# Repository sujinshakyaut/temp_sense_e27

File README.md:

# Thermal Monitoring Module (E27)

A compact multi-channel temperature sensing PCB built around the TI MSPM0C1104 microcontroller with CAN FD communication. Designed to be later integrated on a voltage tap board that mounts directly onto the Orion BMS module, providing up to 24 analog temperature inputs per tapboard or breakout board multiplexed through a 3 ADC channel with robust power protection for automotive and industrial environments.

## Table of Contents

- [Background](#background)
- [NTC Thermistors & Steinhart-Hart](#ntc-thermistors--steinhart-hart)
- [Validation & Troubleshooting](#validation--troubleshooting)
- [Features](#features)
- [Contributing](#contributing)
- [License](#license)

## Background

This is a redesigned temperature sensing board intended to be integrated with a voltage tap board on the Orion BMS module, providing cell temperature monitoring across the battery pack. 

The main Orion BMS is limited to 8 internal thermistor inputs, which is insufficient for large-scale battery packs. To achieve full coverage, we integrated the Orion Thermistor Expansion Module, scaling our monitoring capacity to 60+ individual cells. This expansion node digitizes localized analog temperatures and broadcasts them via CANbus to the main unit. This architecture not only meets the capacity requirements of the accumulator but also ensures clean data transmission and minimizes wiring complexity within the high-voltage enclosure.

The board consolidates power regulation, input protection, analog multiplexing, and CAN FD communication onto a single compact PCB. A three-stage power supply has been implemented due to potential 60V voltage spikes from the battery module. Power input is protected by an LM74500 ideal diode controller and an SMF24CA TVS diode, with the AP63205 buck converter stepping down to 5 V and a TPS7A03 LDO providing a clean 3.3 V rail. A fuse is included for extra protection.

The CLV4051A 8:1 analog multiplexer allows a single ADC input on the MSPM0C to scan up to 8 temperature sensor channels sequentially, reducing pin count. The MCP2517FD provides CAN FD connectivity over SPI.

## NTC Thermistors & Steinhart-Hart

This board interfaces with Negative Temperature Coefficient (NTC) thermistors (typically 10 kΩ at 25°C). The thermistors are placed in a voltage divider circuit with a known 10 kΩ bias resistor. Because the resistance curve of an NTC is highly non-linear, the firmware utilizes the Steinhart-Hart equation for accurate conversion from resistance to temperature across the accumulator's operating range:

$$\frac{1}{T} = A + B \ln(R) + C (\ln(R))^3$$

Where:
* T = Temperature in Kelvin
* R = Measured resistance of the thermistor in Ohms
* A, B, C = Steinhart-Hart coefficients provided by the thermistor manufacturer

The MCU reads the 12-bit ADC value, calculates the resistance R via the voltage divider equation, applies the Steinhart-Hart conversion to find Kelvin, and then broadcasts the Celsius equivalent over CAN FD.

## Features

- 24-channel analog temperature input via CLV4051A multiplexers
- CAN FD communication (MCP2517FD over SPI) to Orion BMS
- Wide input voltage range with reverse polarity and TVS protection
- On-board buck + LDO three-stage power supply with 24V voltage regulation
- High-accuracy NTC thermistor reading using Steinhart-Hart conversion
- Screw terminal connectors
- M3 mounting holes for panel or DIN mount

## Contributing

Open an issue or pull request on [GitHub](https://github.com/sujinshakyaut/temp_sense_e27).

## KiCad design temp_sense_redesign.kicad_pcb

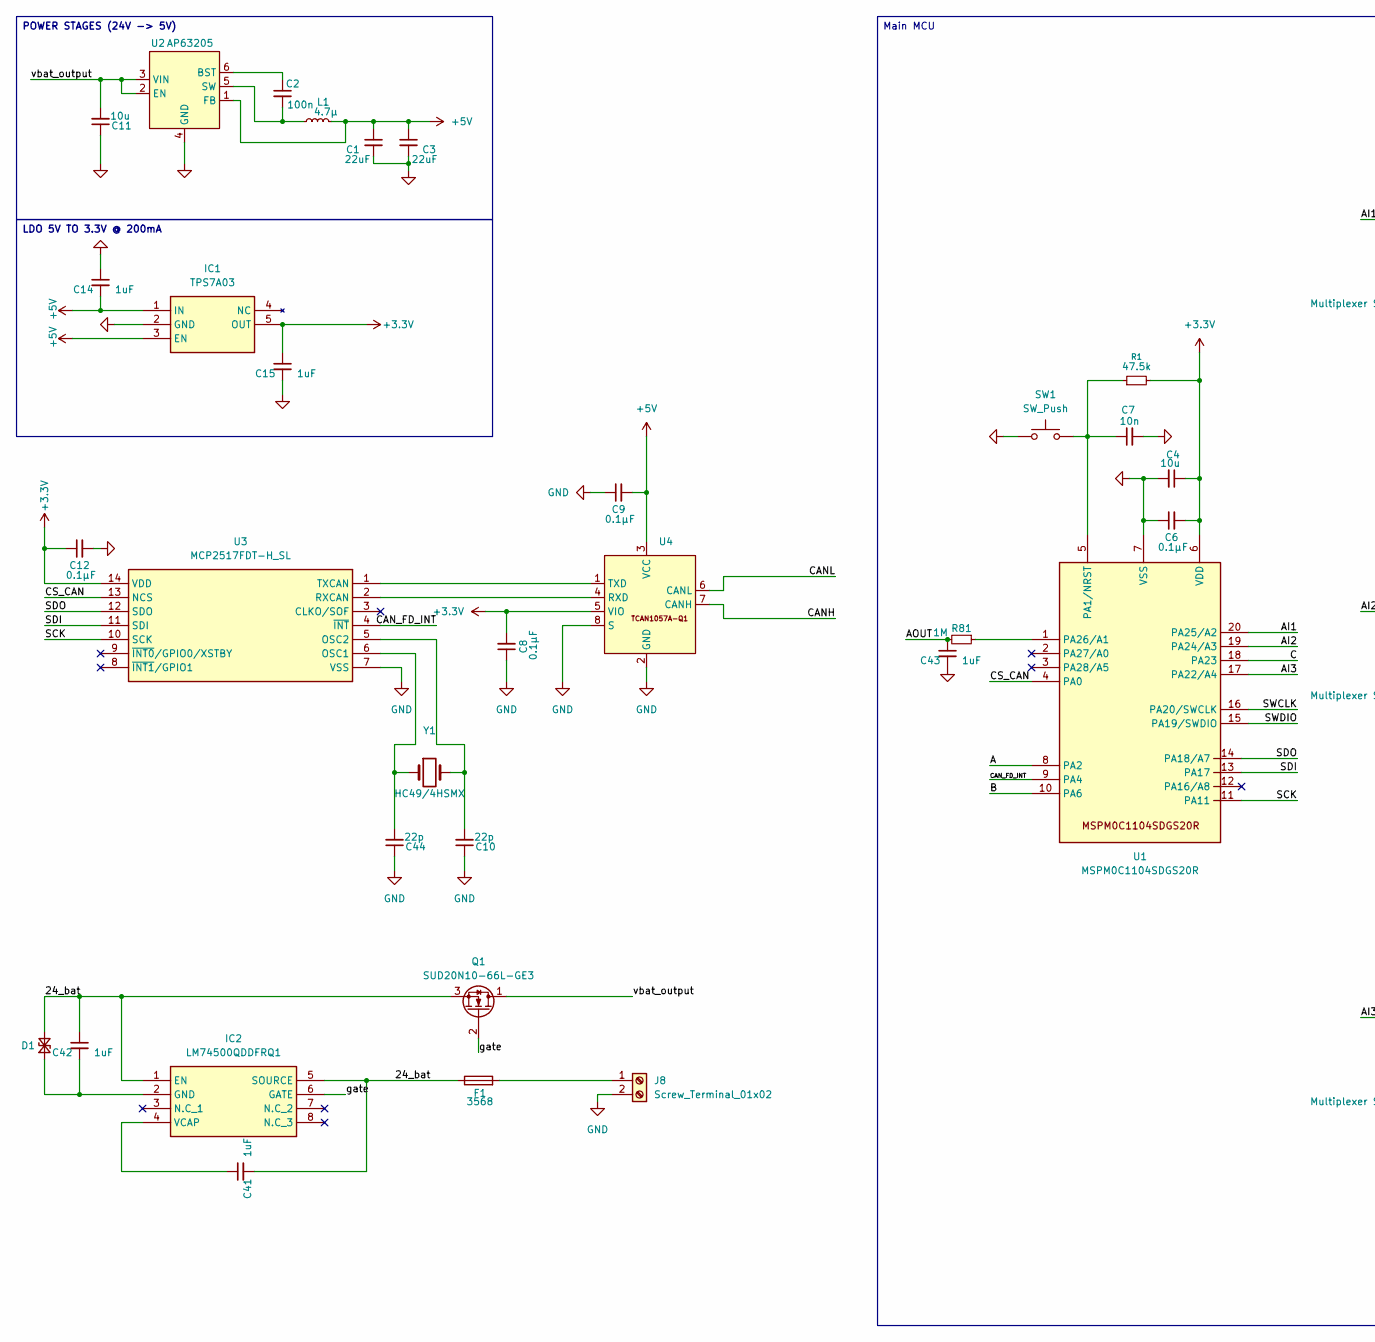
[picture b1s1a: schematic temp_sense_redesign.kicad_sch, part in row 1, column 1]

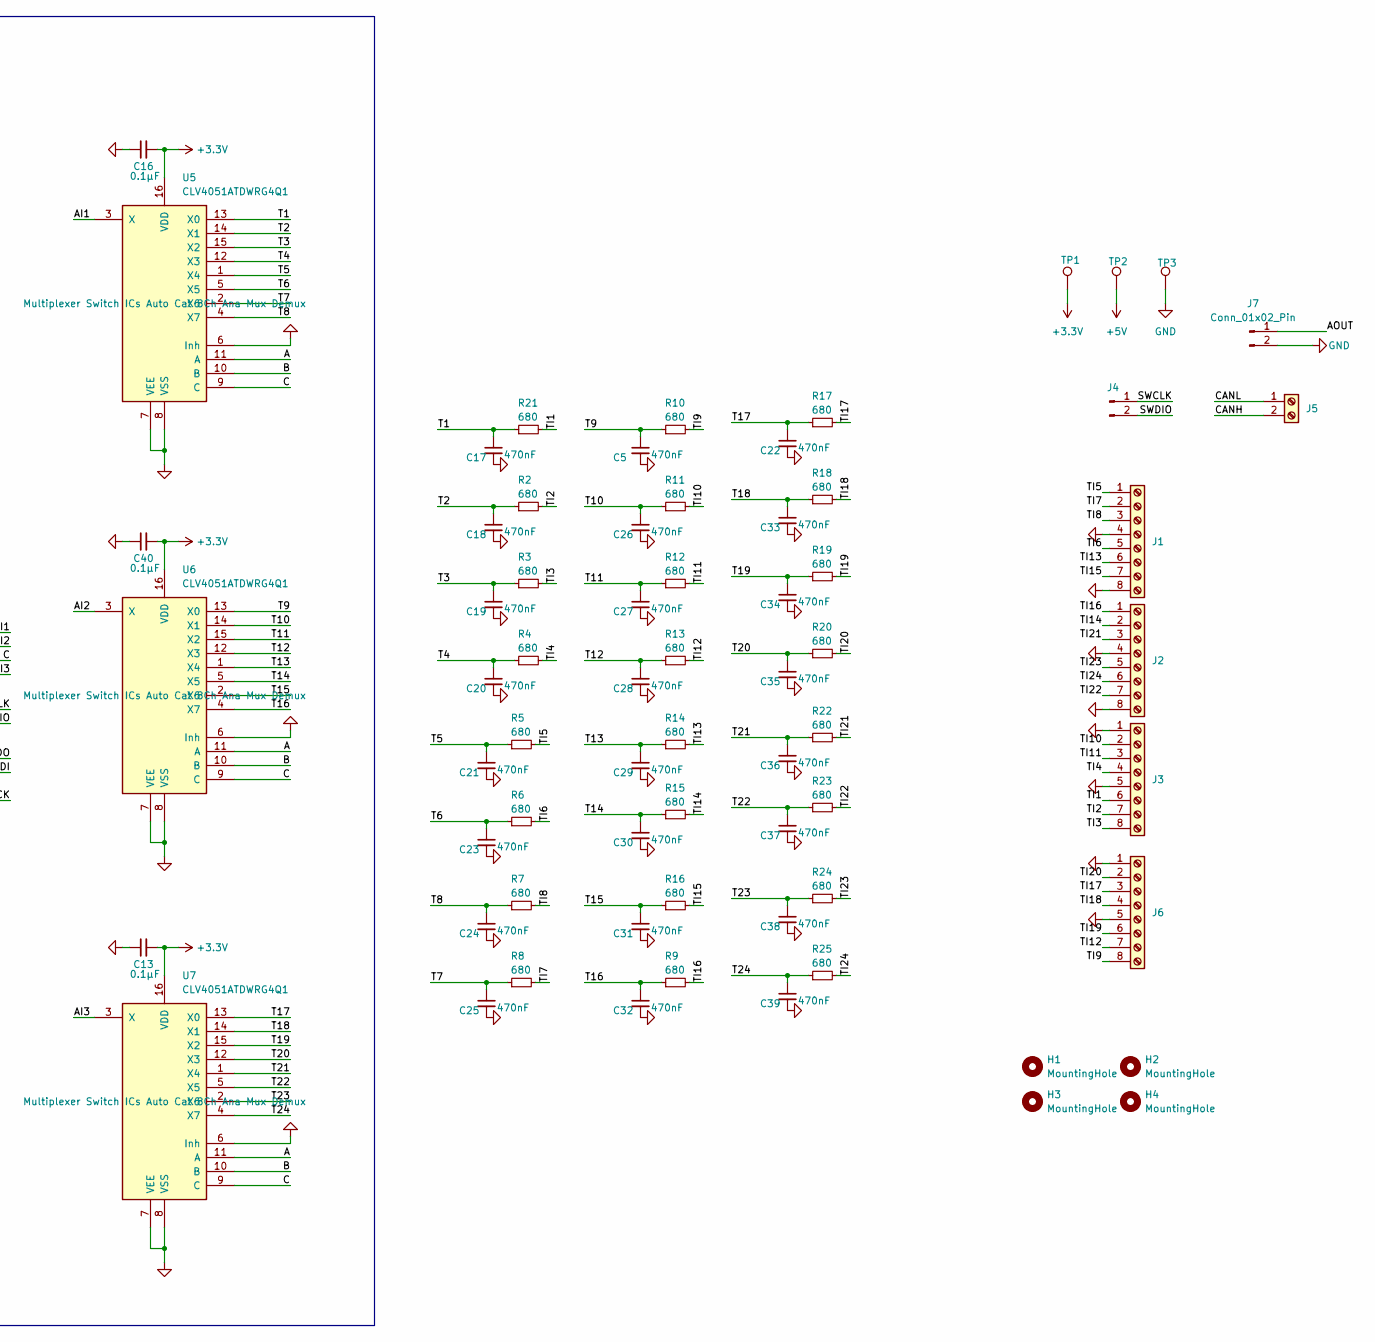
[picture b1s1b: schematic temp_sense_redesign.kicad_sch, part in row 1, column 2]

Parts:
C1, C3: 22uF; C_0603_1608Metric; Mouser P/N 963-MLASG32MSB5226MP
C2: 100n; C_0603_1608Metric; Mouser P/N 810-C1608X8R1H104K
C4: 10u; C_0603_1608Metric; Mouser P/N 81-ZRB18AR6YA106ME1L
C5, C17, C18, C19, C20, C21, C22, C23, C24, C25, C26, C27, C28, C29, C30, C31, C32, C33, C34, C35, C36, C37, C38, C39: 470nF; C_0603_1608Metric; Mouser P/N 81-GXT155R61A474KE1D
C6, C8, C9, C12, C13, C16, C40: 0.1µF; C_0603_1608Metric; Mouser P/N 81-GCM188R71C104KA7J
C7: 10n; C_0603_1608Metric; Mouser P/N 603-CC0603JR7R7BB103
C10, C44: 22p; C_0603_1608Metric; Mouser P/N 81-GCQ0335C1H220JB1D
C11: 10u; C_0603_1608Metric_Pad1.08x0.95mm_HandSolder; Mouser P/N 81-ZRB18AR6YA106ME1L
C14, C15, C41, C42, C43: 1uF; C_0603_1608Metric; Mouser P/N 81-GRM1887R1E105KA2D
D1: Littelfuse SMF24CA; D_SOD-123F; Mouser P/N 576-SMF24CA
F1: 3568; Fuseholder_Blade_Mini_Keystone_3568; Mouser P/N 534-3568
H1, H2, H3, H4: MountingHole; MountingHole_3.2mm_M3
IC1: TPS7A03; SOT-23-5_HandSoldering; Manufacturer_Part_Number TLV74133PDBVR
IC2: LM74500QDDFRQ1; TSOT-23-8_HandSoldering; Mouser P/N 595-LM74500QDDFRQ1
J1, J2, J3, J6: Screw_Terminal_01x08; 1725711; Mouser P/N 490-TB003-500-P03BE
J4, J7: Conn_01x02_Pin; PinSocket_1x02_P2.00mm_Vertical
J5: Screw_Terminal_01x02; 1725656; Mouser P/N 651-1725656
J8: Screw_Terminal_01x02; 1725656
L1: 4.7μ; inductorcustome27; Mouser P/N 70-IHLP2020BZR4R7M1A
Q1: SUD20N10-66L-GE3; SUD20N1066LGE3; Mouser P/N 78-SUD20N10-66L-GE3
R1: 47.5k; R_0603_1608Metric; Mouser P/N 652-CR1206FX-4752ELF
R2, R3, R4, R5, R6, R7, R8, R9, R10, R11, R12, R13, R14, R15, R16, R17, R18, R19, R20, R21, R22, R23, R24, R25: 680; R_0603_1608Metric; Mouser P/N 667-ERJ-3EKF6800V
R81: 1M; R_0603_1608Metric; Mouser P/N 667-ERJ-3EKF1004V
SW1: SW_Push; KSC251JSPDELTALFS; Mouser P/N 611-KSC251JSPDELTALF
TP1, TP2, TP3: TestPoint; TestPoint_Pad_1.5x1.5mm
U1: MSPM0C1104SDGS20R; MSPMOC; Mouser P/N 595-MSPM0C1104SDG20R
U2: AP63205; TSOT-23-6; Mouser P/N 621-AP63205WU-7
U3: MCP2517FDT-H_SL; SOIC-14_3.9x8.7mm_P1.27mm; Mouser P/N 579-MCP2517FD-H/SL
U4: MCP2517FD-H/SL; Texas_DDF0008A_SOT-8_1.6x2.9mm_P0.65mm; Mouser P/N 595-TCAN1057AVDDFRQ1
U5, U6, U7: CLV4051ATDWRG4Q1; SOIC-16W_7.5x10.3mm_P1.27mm; Mouser P/N 595-CLV4051ATDWRG4Q1
Y1: HC49/4HSMX; 830017146; Mouser P/N 710-830017146

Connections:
+3.3V: C4.1, C6.2, C8.2, C12.1, C13.2, C15.1, C16.2, C40.2, IC1.5 (OUT), R1.2, TP1.1, U1.6 (VDD), U3.14 (VDD), U4.5 (VIO), U5.16 (VDD), U6.16 (VDD), U7.16 (VDD)
+5V: C1.1, C3.1, C9.2, C14.2, IC1.1 (IN), IC1.3 (EN), L1.2, TP2.1, U2.1 (FB), U4.3 (VCC)
/24_bat: C41.2, C42.1, D1.2 (A2), F1.1, IC2.1 (EN), IC2.5 (SOURCE), Q1.3 (S)
/A: U1.8 (PA2), U5.11 (A), U6.11 (A), U7.11 (A)
/AI1: U1.20 (PA25/A2), U5.3 (X)
/AI2: U1.19 (PA24/A3), U6.3 (X)
/AI3: U1.17 (PA22/A4), U7.3 (X)
/AOUT: C43.1, J7.1, R81.2
/B: U1.10 (PA6), U5.10 (B), U6.10 (B), U7.10 (B)
/C: U1.18 (PA23), U5.9 (C), U6.9 (C), U7.9 (C)
/CANH: J5.2, U4.7 (CANH)
/CANL: J5.1, U4.6 (CANL)
/CAN_FD_INT: U1.9 (PA4), U3.4 (~INT)
/CS_CAN: U1.4 (PA0), U3.13 (NCS)
/SCK: U1.11 (PA11), U3.10 (SCK)
/SDI: U1.13 (PA17), U3.11 (SDI)
/SDO: U1.14 (PA18/A7), U3.12 (SDO)
/SWCLK: J4.1, U1.16 (PA20/SWCLK)
/SWDIO: J4.2, U1.15 (PA19/SWDIO)
/T1: C17.1, R21.1, U5.13 (X0)
/T2: C18.1, R2.1, U5.14 (X1)
/T3: C19.1, R3.1, U5.15 (X2)
/T4: C20.1, R4.1, U5.12 (X3)
/T5: C21.1, R5.1, U5.1 (X4)
/T6: C23.1, R6.1, U5.5 (X5)
/T7: C25.1, R8.1, U5.2 (X6)
/T8: C24.1, R7.1, U5.4 (X7)
/T9: C5.1, R10.1, U6.13 (X0)
/T10: C26.1, R11.1, U6.14 (X1)
/T11: C27.1, R12.1, U6.15 (X2)
/T12: C28.1, R13.1, U6.12 (X3)
/T13: C29.1, R14.1, U6.1 (X4)
/T14: C30.1, R15.1, U6.5 (X5)
/T15: C31.1, R16.1, U6.2 (X6)
/T16: C32.1, R9.1, U6.4 (X7)
/T17: C22.1, R17.1, U7.13 (X0)
/T18: C33.1, R18.1, U7.14 (X1)
/T19: C34.1, R19.1, U7.15 (X2)
/T20: C35.1, R20.1, U7.12 (X3)
/T21: C36.1, R22.1, U7.1 (X4)
/T22: C37.1, R23.1, U7.5 (X5)
/T23: C38.1, R24.1, U7.2 (X6)
/T24: C39.1, R25.1, U7.4 (X7)
/TI1: J3.6, R21.2
/TI2: J3.7, R2.2
/TI3: J3.8, R3.2
/TI4: J3.4, R4.2
/TI5: J1.1, R5.2
/TI6: J1.5, R6.2
/TI7: J1.2, R8.2
/TI8: J1.3, R7.2
/TI9: J6.8, R10.2
/TI10: J3.2, R11.2
/TI11: J3.3, R12.2
/TI12: J6.7, R13.2
/TI13: J1.6, R14.2
/TI14: J2.2, R15.2
/TI15: J1.7, R16.2
/TI16: J2.1, R9.2
/TI17: J6.3, R17.2
/TI18: J6.4, R18.2
/TI19: J6.6, R19.2
/TI20: J6.2, R20.2
/TI21: J2.3, R22.2
/TI22: J2.7, R23.2
/TI23: J2.5, R24.2
/TI24: J2.6, R25.2
/gate: IC2.6 (GATE), Q1.2 (G)
/vbat_output: C11.2, Q1.1 (D), U2.2 (EN), U2.3 (VIN)
GND: C1.2, C3.2, C4.2, C5.2, C6.1, C7.2, C8.1, C9.1, C10.1, C11.1, C12.2, C13.1, C14.1, C15.2, C16.1, C17.2, C18.2, C19.2, C20.2, C21.2, C22.2, C23.2, C24.2, C25.2, C26.2, C27.2, C28.2, C29.2, C30.2, C31.2, C32.2, C33.2, C34.2, C35.2, C36.2, C37.2, C38.2, C39.2, C40.1, C43.2, C44.1, IC1.2 (GND), J1.4, J1.8, J2.4, J2.8, J3.1, J3.5, J6.1, J6.5, J7.2, J8.2, SW1.1, TP3.1, U1.7 (VSS), U2.4 (GND), U3.7 (VSS), U4.2 (GND), U4.8 (S), U5.6 (Inh), U5.7 (VEE), U5.8 (VSS), U6.6 (Inh), U6.7 (VEE), U6.8 (VSS), U7.6 (Inh), U7.7 (VEE), U7.8 (VSS)
unnamed: C42.2, D1.1 (A1), IC2.2 (GND)
unnamed: C41.1, IC2.4 (VCAP)
unnamed: F1.2, J8.1
unnamed: C7.1, R1.1, SW1.2, U1.5 (PA1/NRST)
unnamed: R81.1, U1.1 (PA26/A1)
unnamed: C2.1, U2.6 (BST)
unnamed: C2.2, L1.1, U2.5 (SW)
unnamed: C44.2, U3.6 (OSC1), Y1.1
unnamed: C10.2, U3.5 (OSC2), Y1.2
unnamed: U3.2 (RXCAN), U4.4 (RXD)
unnamed: U3.1 (TXCAN), U4.1 (TXD)

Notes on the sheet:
LDO 5V TO 3.3V @ 200mA
Main MCU
POWER STAGES (24V -> 5V)

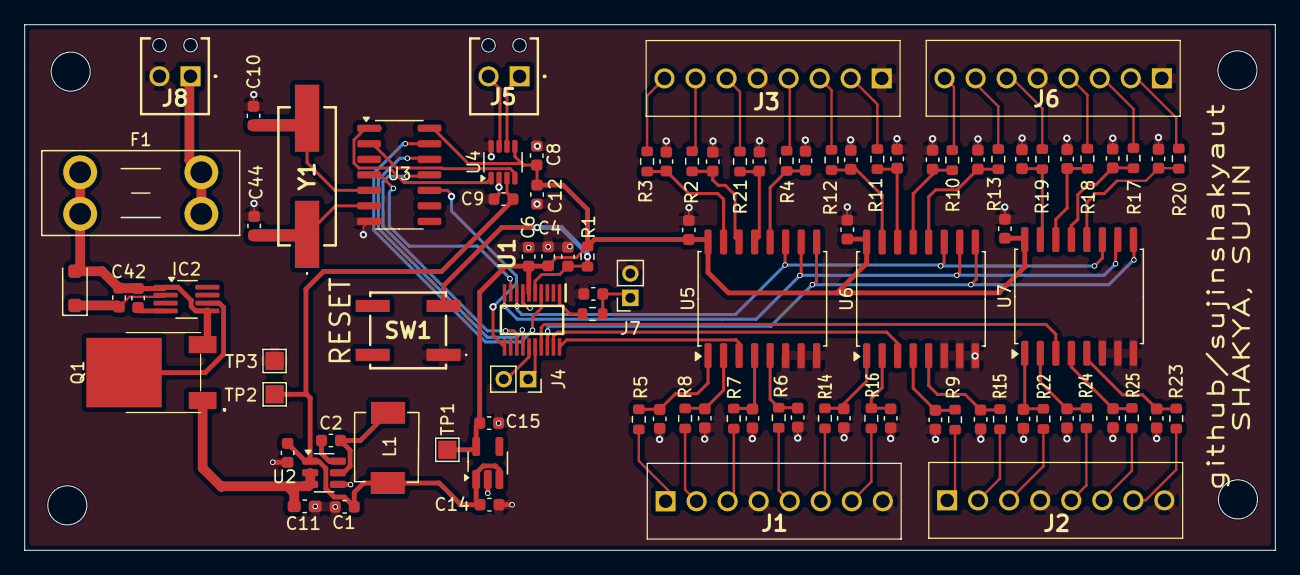
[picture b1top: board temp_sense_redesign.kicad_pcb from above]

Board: 2 copper layers, 102.4 x 43.0 mm, 100 parts (0 on the bottom side), 81 nets.

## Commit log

2026-01-18 main
2026-01-21 final
2026-03-28 Update design files, add custom library and footprints
2026-04-17 Add KiCad .gitignore, remove gerber/backup/cache files from tracking
2026-04-17 Remove symbol library files and ignore *.kicad_sym
2026-04-17 Add README with hardware overview and component table
2026-04-17 Remove Getting Started section from README
    Removed 'Getting Started' section and updated features list.
2026-04-17 Add board image, TI and Orion BMS badges, update BMS context in README
2026-04-17 Use higher quality board render image in README
2026-04-17 Revise README for clarity and additional details
    Updated the README to clarify integration with voltage tap board and added details about the three-stage power supply and fuse protection.
2026-04-17 Enhance README with NTC thermistors and troubleshooting info
    Added sections on NTC thermistors and validation troubleshooting to provide detailed information on temperature sensing and system reliability.
2026-04-17 Revise README for temperature sensing PCB details
    Updated description to reflect integration capabilities and increased temperature input support.
2026-04-17 Enhance README with integration details
    Added section on Decentralization and Orion BMS Integration to explain the benefits of the PCB design and its communication method.
2026-04-17 Update README to simplify image display
    Removed unnecessary HTML tags around the image in the README.
2026-04-17 Remove fp-lib-table, sym-lib-table, and old board render PNG
2026-04-17 Increase image width for temperature sensing board
    Updated image size for better visibility in README.
2026-04-17 Revise README with expansion module details and format
    Updated the background section to include details about the Orion Thermistor Expansion Module and its capabilities. Revised the hardware table format and corrected the number of temperature channels 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
2026-04-18 Remove hardware and validation sections from README
    Removed hardware specifications and validation sections from README.
2026-04-18 Rename project to Thermal Monitoring Module (E27)
2026-04-18 Adjust image width in README.md
    Updated image size in README for better clarity.
2026-04-18 Refactor background section in README.md
    Removed duplicate text in the background section for clarity.
2026-04-18 Remove 'Hardware' from table of contents
    Removed 'Hardware' section from the table of contents.

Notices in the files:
README.md:
License: MIT
